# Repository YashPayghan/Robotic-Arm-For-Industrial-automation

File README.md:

# 🤖 Robotic Arm for Industrial Automation

## 📌 Overview

This project presents a microcontroller-based robotic arm designed for industrial automation applications such as pick-and-place and material handling.

The system controls multiple robotic-arm joints and a gripper to achieve controlled and repeatable movement. Embedded firmware is used to control motor movement, joint positioning, and the overall sequence of operation.

## 🎯 Objectives

- Develop a low-cost robotic arm for industrial automation.
- Control multiple joints with precise movement.
- Implement automated pick-and-place operations.
- Control the gripper for object handling.
- Improve repeatability and accuracy of robotic movement.
- Provide a foundation for industrial automation applications.

## ⚙️ Features

- Multi-axis robotic arm control
- Individual joint movement
- Precise angular positioning
- Gripper control
- Pick-and-place operation
- Adjustable motor speed
- Programmed movement sequences
- Manual/automatic operation
- Safety and limit control

## 🔧 Hardware Requirements

- Microcontroller
- Servo/Stepper motors
- Motor drivers
- Robotic arm mechanism
- Gripper
- Power supply
- Limit switches/sensors
- Connecting wires
- Breadboard/PCB

> Replace this list with the exact components used in the project.

## 💻 Software Requirements

- Arduino IDE / PlatformIO
- Embedded C/C++
- Microcontroller programming environment

## 🧠 Working Principle

1. The microcontroller receives movement commands.
2. The controller generates appropriate signals for the motors.
3. Individual joints move according to the programmed position and speed.
4. The robotic arm reaches the required position.
5. The gripper picks or releases the object.
6. The arm follows the programmed sequence to complete the operation.
7. Sensors or limit switches provide position and safety feedback where implemented.

## 📊 Applications

- Industrial pick-and-place
- Material handling
- Assembly operations
- Sorting systems
- Laboratory automation
- Educational robotics
- Small-scale manufacturing automation

## 🚀 Future Improvements

- Closed-loop position control
- Computer vision-based object detection
- Conveyor-belt integration
- Wireless control
- Inverse kinematics
- ROS integration
- Automatic path planning
- Industrial communication using CAN/Modbus

## 🛠️ Technologies

- Embedded C/C++
- Microcontroller
- Motor Control
- PWM
- GPIO
- Sensors
- Robotics
- Industrial Automation

## 👨‍💻 Project Team

Add your team members here.

## 📄 License

This project is developed for educational and academic purposes.# 🤖 Robotic Arm for Industrial Automation

## 📌 Overview

This project presents a microcontroller-based robotic arm designed for industrial automation applications such as pick-and-place and material handling.

The system controls multiple robotic-arm joints and a gripper to achieve controlled and repeatable movement. Embedded firmware is used to control motor movement, joint positioning, and the overall sequence of operation.

## 🎯 Objectives

- Develop a low-cost robotic arm for industrial automation.
- Control multiple joints with precise movement.
- Implement automated pick-and-place operations.
- Control the gripper for object handling.
- Improve repeatability and accuracy of robotic movement.
- Provide a foundation for industrial automation applications.

## ⚙️ Features

- Multi-axis robotic arm control
- Individual joint movement
- Precise angular positioning
- Gripper control
- Pick-and-place operation
- Adjustable motor speed
- Programmed movement sequences
- Manual/automatic operation
- Safety and limit control

## 🔧 Hardware Requirements

- Microcontroller
- Servo/Stepper motors
- Motor drivers
- Robotic arm mechanism
- Gripper
- Power supply
- Limit switches/sensors
- Connecting wires
- Breadboard/PCB

> Replace this list with the exact components used in the project.

## 💻 Software Requirements

- Arduino IDE / PlatformIO
- Embedded C/C++
- Microcontroller programming environment

## 🧠 Working Principle

1. The microcontroller receives movement commands.
2. The controller generates appropriate signals for the motors.
3. Individual joints move according to the programmed position and speed.
4. The robotic arm reaches the required position.
5. The gripper picks or releases the object.
6. The arm follows the programmed sequence to complete the operation.
7. Sensors or limit switches provide position and safety feedback where implemented.

## 📊 Applications

- Industrial pick-and-place
- Material handling
- Assembly operations
- Sorting systems
- Laboratory automation
- Educational robotics
- Small-scale manufacturing automation

## 🚀 Future Improvements

- Closed-loop position control
- Computer vision-based object detection
- Conveyor-belt integration
- Wireless control
- Inverse kinematics
- ROS integration
- Automatic path planning
- Industrial communication using CAN/Modbus

## 🛠️ Technologies

- Embedded C/C++
- Microcontroller
- Motor Control
- PWM
- GPIO
- Sensors
- Robotics
- Industrial Automation

## 👨‍💻 Project Team

Add your team members here.

## 📄 License

This project is developed for educational and academic purposes.

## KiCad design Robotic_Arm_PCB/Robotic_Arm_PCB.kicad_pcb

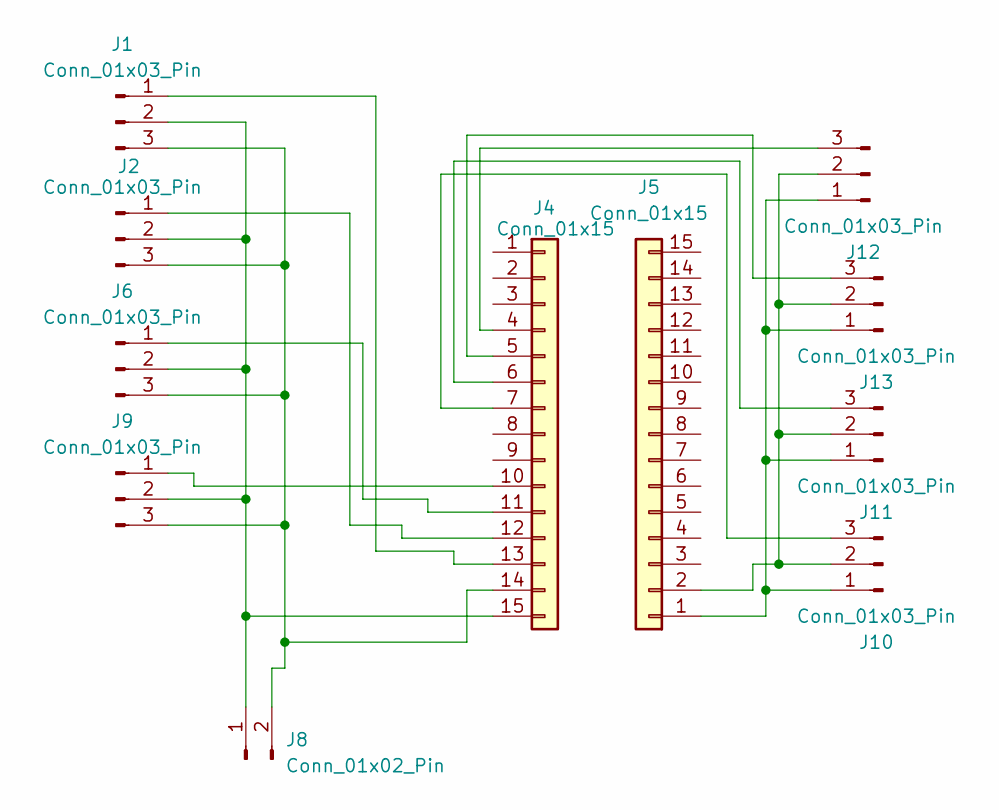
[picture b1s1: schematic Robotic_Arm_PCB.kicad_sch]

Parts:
J1, J2, J6, J9, J10, J11, J12, J13: Conn_01x03_Pin; PinHeader_1x03_P2.54mm_Vertical
J4, J5: Conn_01x15; PinHeader_1x15_P2.54mm_Vertical
J8: Conn_01x02_Pin; PinHeader_1x02_P2.54mm_Vertical

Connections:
unnamed: J1.1, J4.13
unnamed: J1.2, J2.2, J4.15 (vin), J6.2, J8.1, J9.2
unnamed: J1.3, J2.3, J4.14 (gnd), J6.3, J8.2, J9.3
unnamed: J2.1, J4.12
unnamed: J4.11 (ss14), J6.1
unnamed: J4.10 (ss27), J9.1
unnamed: J5.1, J10.1, J11.1, J12.1, J13.1
unnamed: J5.2, J10.2, J11.2, J12.2, J13.2
unnamed: J4.7 (adc33), J10.3
unnamed: J4.6 (adc32), J11.3
unnamed: J4.4 (adc34), J12.3
unnamed: J4.5 (adc35), J13.3

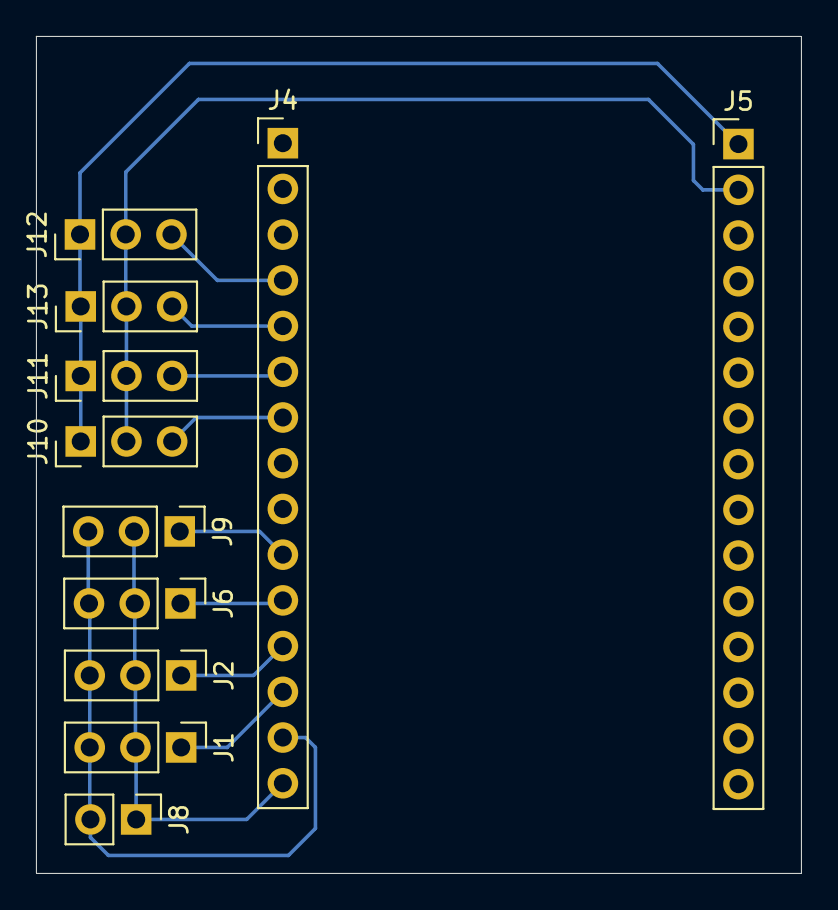
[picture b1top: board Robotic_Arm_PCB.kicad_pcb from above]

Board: 2 copper layers, 42.5 x 46.5 mm, 11 parts (0 on the bottom side), 12 nets.

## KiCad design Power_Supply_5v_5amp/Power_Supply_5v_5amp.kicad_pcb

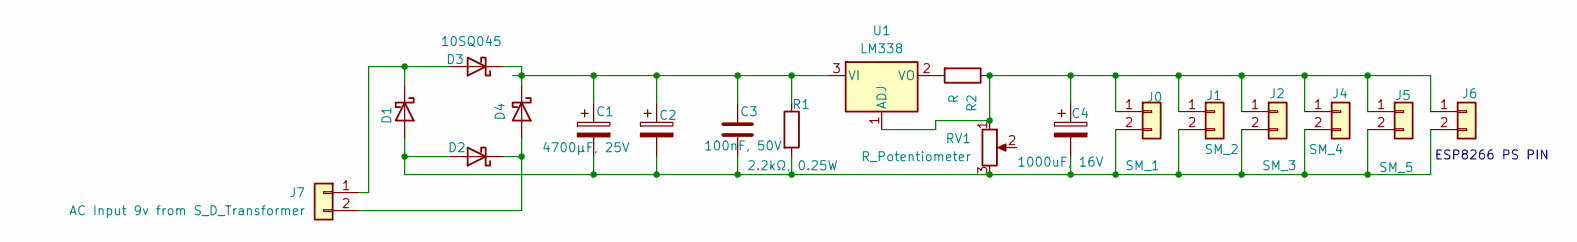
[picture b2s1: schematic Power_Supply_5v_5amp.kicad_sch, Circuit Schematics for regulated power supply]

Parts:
C1: 4700µF, 25V; CP_Radial_D18.0mm_P7.50mm
C2: CP_Radial_D18.0mm_P7.50mm
C3: 100nF, 50V; C_Disc_D5.0mm_W2.5mm_P5.00mm
C4: 1000uF, 16V; CP_Radial_D10.0mm_P5.00mm
D1, D2, D4: D_P600_R-6_P12.70mm_Horizontal
D3: 10SQ045; D_P600_R-6_P12.70mm_Horizontal
J0: SM_1; PhoenixContact_MC_1,5_2-G-5.08_1x02_P5.08mm_Horizontal
J1: SM_2; PhoenixContact_MCV_1,5_2-G-5.08_1x02_P5.08mm_Vertical
J2: SM_3; PhoenixContact_MCV_1,5_2-G-5.08_1x02_P5.08mm_Vertical
J4: SM_4; PhoenixContact_MCV_1,5_2-G-5.08_1x02_P5.08mm_Vertical
J5: SM_5; PhoenixContact_MCV_1,5_2-G-5.08_1x02_P5.08mm_Vertical
J6: SM_6; PhoenixContact_MCV_1,5_2-G-5.08_1x02_P5.08mm_Vertical
J7: AC Input 9v from S_D_Transformer; PhoenixContact_MCV_1,5_2-G-5.08_1x02_P5.08mm_Vertical
R1: 2.2kΩ, 0.25W; R_Axial_DIN0207_L6.3mm_D2.5mm_P10.16mm_Horizontal
R2: R; R_Axial_DIN0207_L6.3mm_D2.5mm_P10.16mm_Horizontal
RV1: R_Potentiometer; Potentiometer_Bourns_3296W_Vertical
U1: LM338; TO-220-3_Vertical

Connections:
unnamed: C1.2, C2.2, C3.2, C4.2, D1.2 (A), D2.2 (A), J0.2, J1.2, J2.2, J4.2, J5.2, J6.2, R1.2, RV1.3
unnamed: D1.1 (K), D3.2 (A), J7.1
unnamed: D2.1 (K), D4.2 (A), J7.2
unnamed: C1.1, C2.1, C3.1, D3.1 (K), D4.1 (K), R1.1, U1.3 (VI)
unnamed: C4.1, J0.1, J1.1, J2.1, J4.1, J5.1, J6.1, R2.1, RV1.1, U1.1 (ADJ)
unnamed: R2.2, U1.2 (VO)

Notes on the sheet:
ESP8266 PS PIN

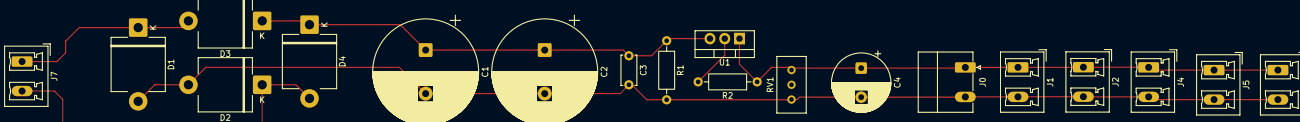
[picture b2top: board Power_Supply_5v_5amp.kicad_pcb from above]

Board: 2 copper layers, 19 parts (0 on the bottom side), 6 nets.
